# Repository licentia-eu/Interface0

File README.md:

# Interface0
ZX Spectrum expansion board base on Raspberry Pi Zero

# Similar projects
 * [ZXInterfaceZ](https://github.com/alvieboy/ZXInterfaceZ) - a fantastic expansion card for the ZX Spectrum which supports tons of features.
 * [Spectranet](https://github.com/spectrumero/spectranet) - another fantastic expansion card for the ZX Spectrum.

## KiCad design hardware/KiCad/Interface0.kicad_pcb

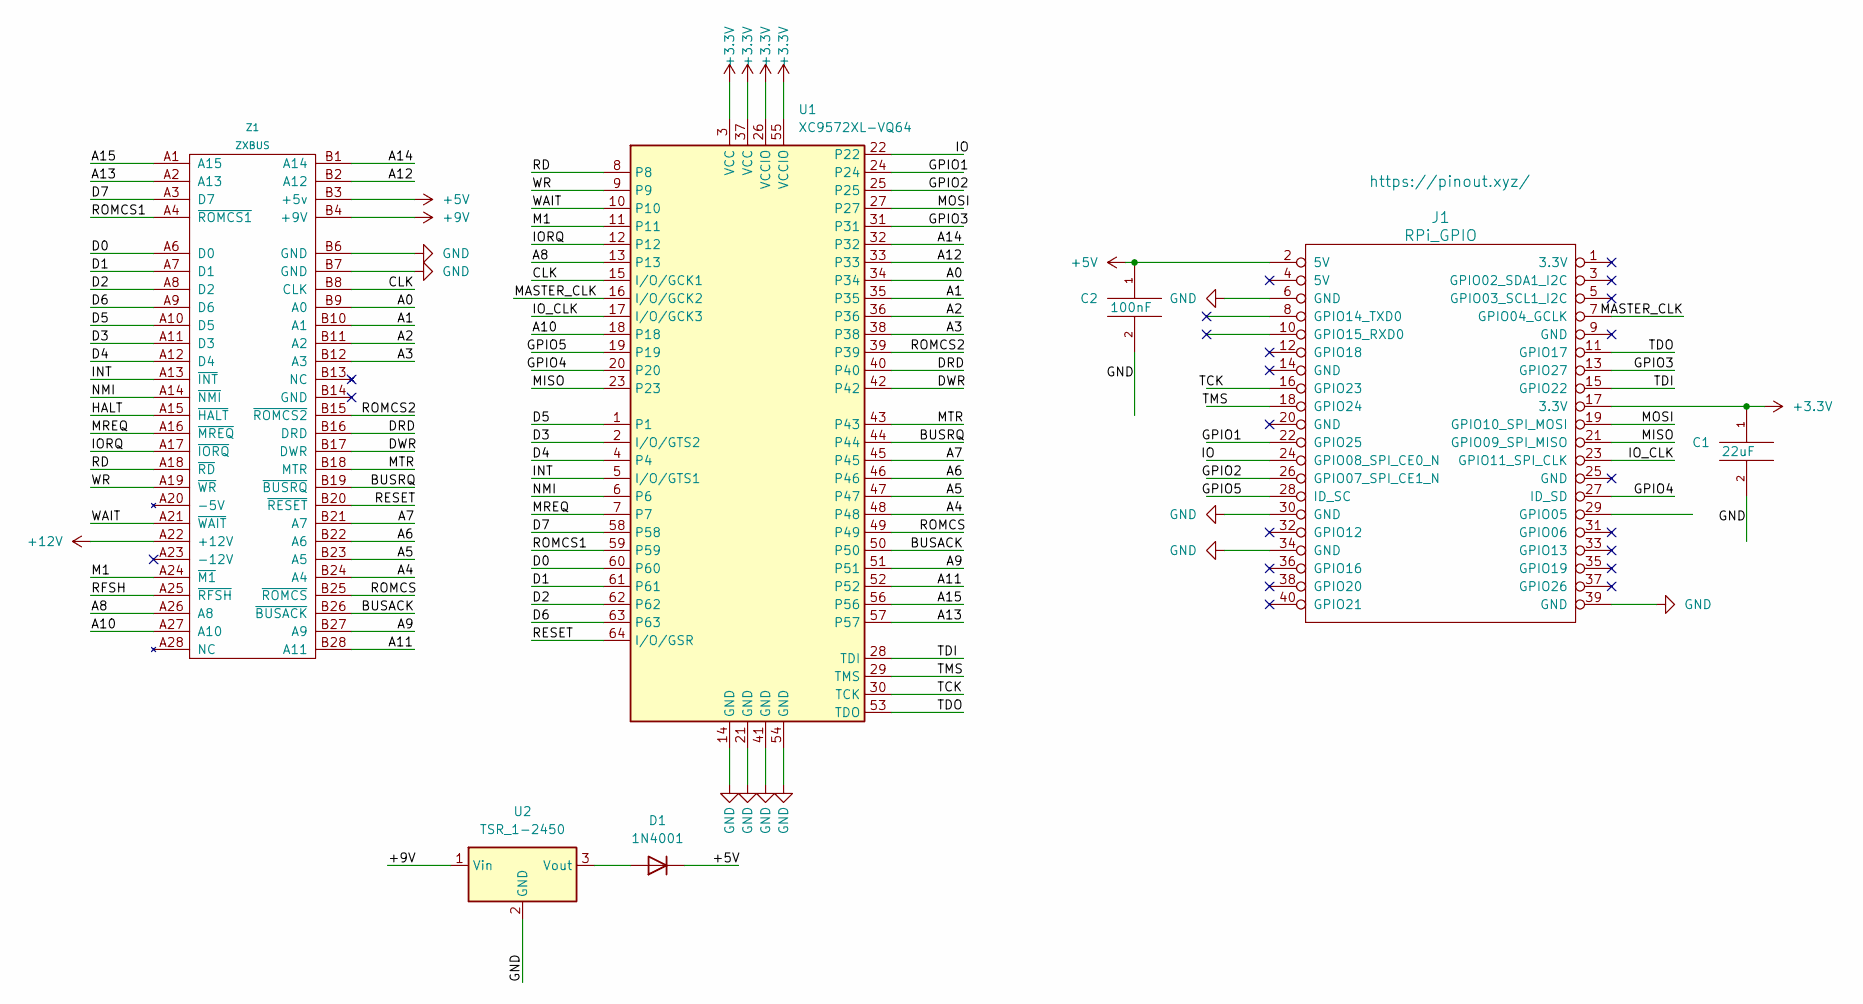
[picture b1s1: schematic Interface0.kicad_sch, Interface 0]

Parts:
C1: 22uF; CP_Radial_Tantal_D7.0mm_P2.50mm
C2: 100nF; CP_Radial_Tantal_D5.0mm_P2.50mm
D1: 1N4001; D_DO-41_SOD81_P10.16mm_Horizontal
J1: RPi_GPIO; Samtec_HLE-120-02-xx-DV-TE_2x20_P2.54mm_Horizontal
U1: XC9572XL-VQ64; TQFP-64_10x10mm_P0.5mm
U2: TSR_1-2450; Converter_DCDC_TRACO_TSR-1_THT
Z1: ZXBUS; ZX_Bus_Edge_Connector

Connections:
+3V3: C1.1, J1.17 (3.3V), U1.3 (VCC), U1.26 (VCCIO), U1.37 (VCC), U1.55 (VCCIO)
+5V: C2.1, D1.1 (K), J1.2 (5V), Z1.B3 (+5v)
+9V: U2.1 (Vin), Z1.B4 (+9V)
+12V: Z1.A22 (+12V)
/A0: U1.34, Z1.B9 (A0)
/A1: U1.35, Z1.B10 (A1)
/A2: U1.36, Z1.B11 (A2)
/A3: U1.38, Z1.B12 (A3)
/A4: U1.48, Z1.B24 (A4)
/A5: U1.47, Z1.B23 (A5)
/A6: U1.46, Z1.B22 (A6)
/A7: U1.45, Z1.B21 (A7)
/A8: U1.13, Z1.A26 (A8)
/A9: U1.51, Z1.B27 (A9)
/A10: U1.18, Z1.A27 (A10)
/A11: U1.52, Z1.B28 (A11)
/A12: U1.33, Z1.B2 (A12)
/A13: U1.57, Z1.A2 (A13)
/A14: U1.32, Z1.B1 (A14)
/A15: U1.56, Z1.A1 (A15)
/BUSACK: U1.50, Z1.B26 (~BUSACK)
/BUSRQ: U1.44, Z1.B19 (~BUSRQ)
/CLK: U1.15 (I/O/GCK1), Z1.B8 (CLK)
/D0: U1.60, Z1.A6 (D0)
/D1: U1.61, Z1.A7 (D1)
/D2: U1.62, Z1.A8 (D2)
/D3: U1.2 (I/O/GTS2), Z1.A11 (D3)
/D4: U1.4, Z1.A12 (D4)
/D5: U1.1, Z1.A10 (D5)
/D6: U1.63, Z1.A9 (D6)
/D7: U1.58, Z1.A3 (D7)
/DRD: U1.40, Z1.B16 (DRD)
/DWR: U1.42, Z1.B17 (DWR)
/GPIO1: J1.22 (GPIO25), U1.24
/GPIO2: J1.26 (GPIO07_SPI_CE1_N), U1.25
/GPIO3: J1.13 (GPIO27), U1.31
/GPIO4: J1.27 (ID_SD), U1.20
/GPIO5: J1.28 (ID_SC), U1.19
/HALT: Z1.A15 (~HALT)
/INT: U1.5 (I/O/GTS1), Z1.A13 (~INT)
/IO: J1.24 (GPIO08_SPI_CE0_N), U1.22
/IORQ: U1.12, Z1.A17 (~IORQ)
/IO_CLK: J1.23 (GPIO11_SPI_CLK), U1.17 (I/O/GCK3)
/M1: U1.11, Z1.A24 (~M1)
/MASTER_CLK: J1.7 (GPIO04_GCLK), U1.16 (I/O/GCK2)
/MISO: J1.21 (GPIO09_SPI_MISO), U1.23
/MOSI: J1.19 (GPIO10_SPI_MOSI), U1.27
/MREQ: U1.7, Z1.A16 (~MREQ)
/MTR: U1.43, Z1.B18 (MTR)
/NMI: U1.6, Z1.A14 (~NMI)
/RD: U1.8, Z1.A18 (~RD)
/RESET: U1.64 (I/O/GSR), Z1.B20 (~RESET)
/RFSH: Z1.A25 (~RFSH)
/ROMCS: U1.49, Z1.B25 (~ROMCS)
/ROMCS1: U1.59, Z1.A4 (~ROMCS1)
/ROMCS2: U1.39, Z1.B15 (~ROMCS2)
/TCK: J1.16 (GPIO23), U1.30 (TCK)
/TDI: J1.15 (GPIO22), U1.28 (TDI)
/TDO: J1.11 (GPIO17), U1.53 (TDO)
/TMS: J1.18 (GPIO24), U1.29 (TMS)
/WAIT: U1.10, Z1.A21 (~WAIT)
/WR: U1.9, Z1.A19 (~WR)
GND: C1.2, C2.2, J1.6 (GND), J1.30 (GND), J1.34 (GND), J1.39 (GND), U1.14 (GND), U1.21 (GND), U1.41 (GND), U1.54 (GND), U2.2 (GND), Z1.B6 (GND), Z1.B7 (GND)
unnamed: D1.2 (A), U2.3 (Vout)

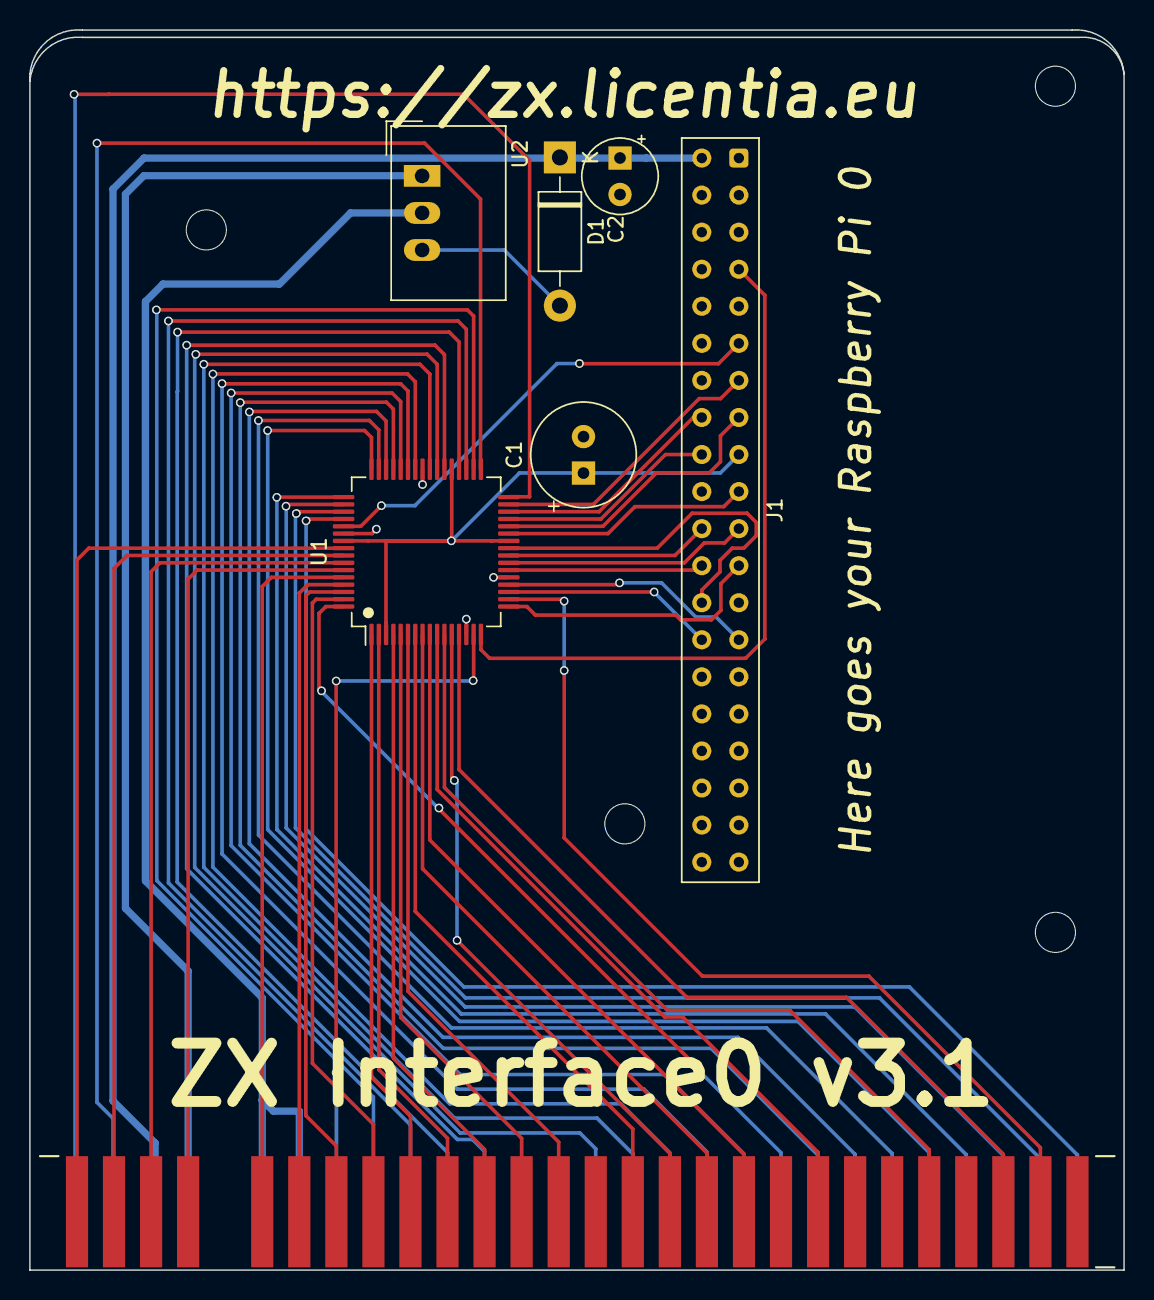
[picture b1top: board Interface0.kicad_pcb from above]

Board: 2 copper layers, 75.0 x 85.0 mm, 7 parts (0 on the bottom side), 61 nets.

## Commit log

2022-04-03 Initial hardware sketch
2022-04-04 Switch to verilog as it's closer to C/C++
2022-04-19 Incorporate Álvaro Lopes tips
    - connect MREQ/IOREQ & SPI_CLK to GCKx
    - connect RESET to GSR
    - restucture the other pins to make it cleaner
2022-04-22 Update net
2022-05-02 Prepare for first release
2022-05-29 PI_CE0 acts as a clock and we must wire it to a clock pin
    Wire the Z80 CPU clock to the remaing one.
2022-06-03 Use custom IO protocol
    Use GPCLK1 as a master clock
2022-06-08 Nuke HALT & RFSH and connect them to RPi
    Add first verilog implementation
2022-06-08 Fix InterfaceZ url
2022-06-09 Switch p25 with p23 to free one FB from FB4
2022-09-24 Swap p25 with p23 to free one FB from FB4
2022-09-24 Add placeholders for server & z80 apps
2022-09-24 WIP: Swtch back to SPI
